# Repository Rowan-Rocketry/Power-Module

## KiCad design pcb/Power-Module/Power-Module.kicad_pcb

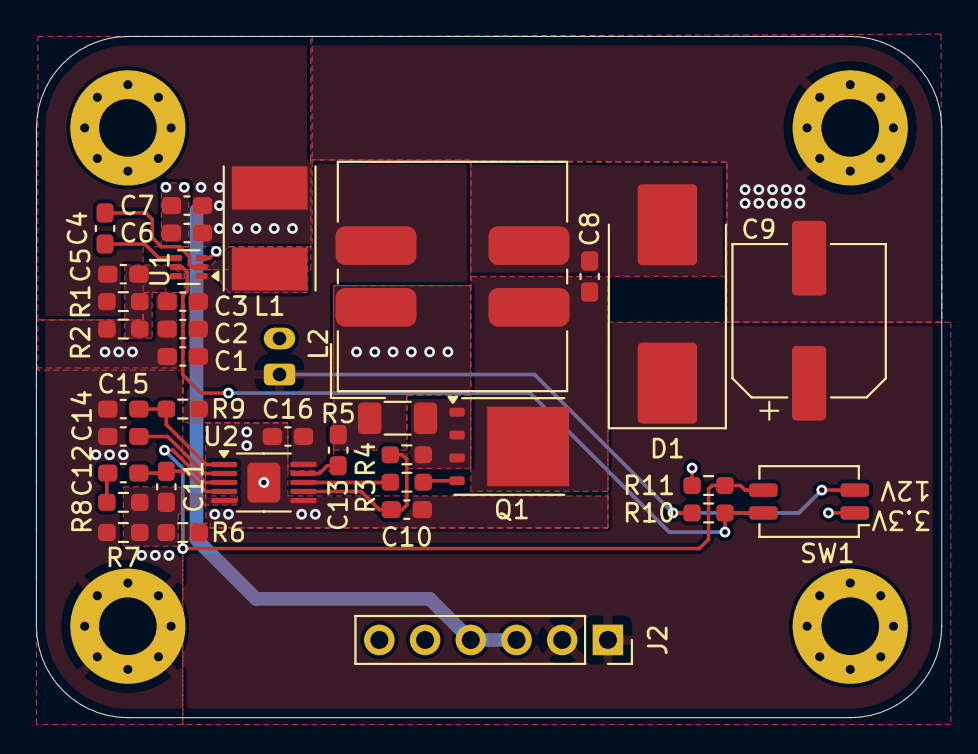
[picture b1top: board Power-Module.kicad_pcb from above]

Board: 2 copper layers, 50.3 x 37.8 mm, 40 parts (1 on the bottom side), 21 nets.

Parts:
C1, C2: 10uF; C_0603_1608Metric_Pad1.08x0.95mm_HandSolder
C3, C4: 100nF; C_0603_1608Metric_Pad1.08x0.95mm_HandSolder
C5: 22pF; C_0603_1608Metric_Pad1.08x0.95mm_HandSolder
C6, C7: 22uF; C_0603_1608Metric_Pad1.08x0.95mm_HandSolder
C8: 4.7uF; C_0603_1608Metric_Pad1.08x0.95mm_HandSolder
C9: 25SVPF100M; CP_Elec_8x6.9
C10: 100pF; C_0603_1608Metric_Pad1.08x0.95mm_HandSolder
C11: 56pF; C_0603_1608Metric_Pad1.08x0.95mm_HandSolder
C12: 5.6nF; C_0603_1608Metric_Pad1.08x0.95mm_HandSolder
C13: 1uF; C_0603_1608Metric_Pad1.08x0.95mm_HandSolder
C14: 68nF; C_0603_1608Metric_Pad1.08x0.95mm_HandSolder
C15: 120pF; C_0603_1608Metric_Pad1.08x0.95mm_HandSolder
C16: 8.2uF; C_0603_1608Metric_Pad1.08x0.95mm_HandSolder
D1: B560C-13-F; D_SMC_Handsoldering
H1, H2, H3, H4: MountingHole_Pad; MountingHole_3.2mm_M3_Pad_Via
J1: Conn_01x02; JST_PH_B2B-PH-K_1x02_P2.00mm_Vertical
J2: Conn_01x06_Socket; PinSocket_1x06_P2.54mm_Vertical
L1: NRS5030T3R3MMGJ; L_Taiyo-Yuden_NR-50xx_HandSoldering
L2: SRF1260-6R8Y; L_Bourns_SRF1260
Q1: CSD18534Q5A; TDSON-8-1
R1: 30.9k; R_0603_1608Metric_Pad0.98x0.95mm_HandSolder
R2, R10, R11: 10k; R_0603_1608Metric_Pad0.98x0.95mm_HandSolder
R3: 11.3; R_0603_1608Metric_Pad0.98x0.95mm_HandSolder
R4: 1k; R_0603_1608Metric_Pad0.98x0.95mm_HandSolder
R5: 12m; R_1206_3216Metric_Pad1.30x1.75mm_HandSolder
R6: 215k; R_0603_1608Metric_Pad0.98x0.95mm_HandSolder
R7: 4.75k; R_0603_1608Metric_Pad0.98x0.95mm_HandSolder
R8: 18.7k; R_0603_1608Metric_Pad0.98x0.95mm_HandSolder
R9: 162k; R_0603_1608Metric_Pad0.98x0.95mm_HandSolder
SW1: SW_DIP_x02; SW_DIP_SPSTx02_Slide_Copal_CHS-02A_W5.08mm_P1.27mm_JPin
U1: TPS562202; SOT-563
U2: TPS40211; VSSOP-10_3x3mm_P0.5mm

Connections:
+3.3V: C5.1, C6.1, C7.1, J2.3, J2.4, L1.2, R1.1
+12V: C9.1, D1.1 (K), J2.1, J2.2, R6.2
/3.3V Buck/Feedback: C5.2, R1.2, R2.1, U1.6 (VFB)
/3.3V Buck/Switch: C4.2, L1.1, U1.2 (SW)
/3.3V Enable: R10.1, SW1.4, U1.5 (EN)
/12V Disable: R11.2, SW1.3, U2.3 (DIS)
/12V SEPIC/Comp: C11.2, C12.2, U2.4 (COMP)
/12V SEPIC/Feedback: C11.1, R6.1, R7.2, R8.2, U2.5 (FB)
/12V SEPIC/Gate Drive: R3.1, U2.8 (GDRV)
/12V SEPIC/I Sense: C10.1, R4.1, U2.7 (ISNS)
GNDA: C1.2, C2.2, C3.2, C6.2, C7.2, C9.2, C10.2, C13.1, C14.2, C15.1, C16.2, H1.1, H2.1, H3.1, H4.1, J1.2, J2.5, J2.6, L2.1, R2.2, R5.1, R7.1, R11.1, SW1.1, U1.3 (GND), U2.6 (GND), U2.11 (GND)
unnamed: C12.1, R8.1
unnamed: C8.2, D1.2 (A), L2.3
unnamed: C8.1, L2.4, Q1.5 (D)
unnamed: Q1.4 (G), R3.2
unnamed: Q1.1 (S), Q1.2 (S), Q1.3 (S), R4.2, R5.2
unnamed: C4.1, U1.4 (VBST)
unnamed: C13.2, U2.9 (BP)
unnamed: C15.2, R9.2, U2.1 (RC)
unnamed: C14.1, U2.2 (SS)
VDD: C1.1, C2.1, C3.1, C16.1, J1.1, L2.2, R9.1, R10.2, SW1.2, U1.1 (VIN), U2.10 (VDD)

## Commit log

2025-05-17 Created system-level hierarch. Implemented 3.3V buck converter based on TI WEBBENCH Power Designer.
2025-05-19 12V and 3.3V supplies in correct form factor
    Completed layout of 3.3V out buck converter and 12V out SEPIC converter. Layout fits on board with the same shape and hole pattern as the rev 1 Ride-Along Module.
